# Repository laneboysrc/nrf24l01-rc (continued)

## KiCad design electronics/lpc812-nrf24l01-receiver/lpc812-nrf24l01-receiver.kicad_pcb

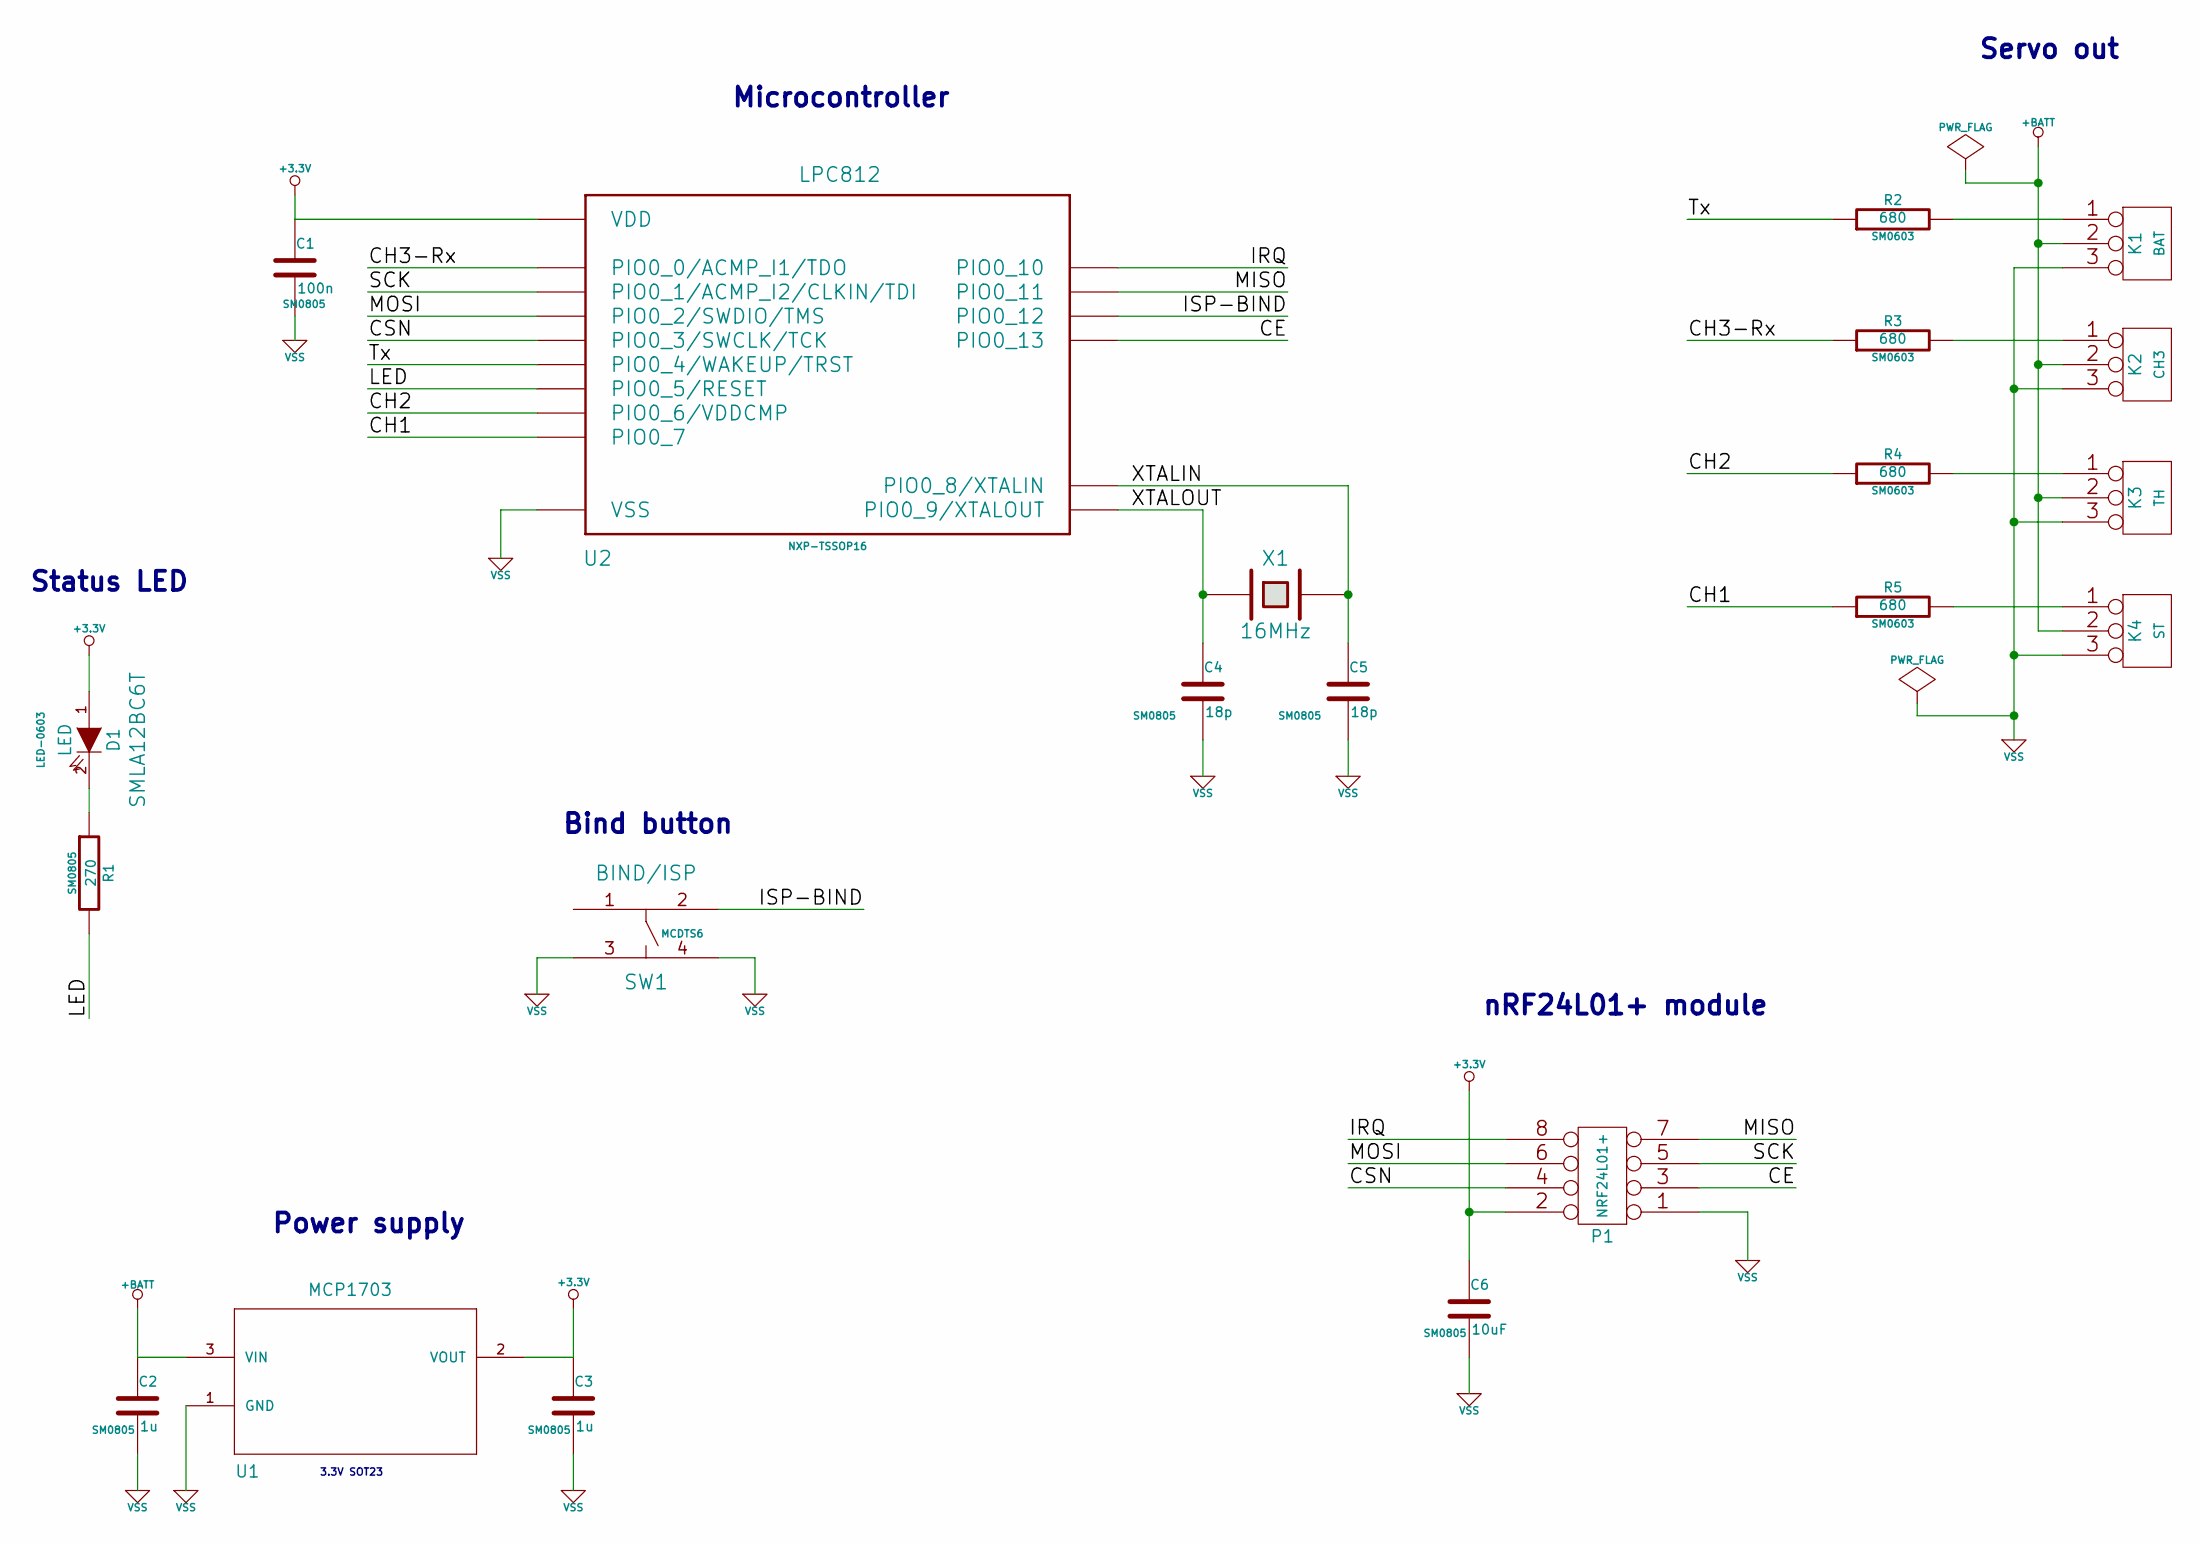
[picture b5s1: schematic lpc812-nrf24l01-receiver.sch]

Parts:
C1: 100n; SM0805
C2, C3: 1u; SM0805
C4, C5: 18p; SM0805
C6: 10uF; SM0805
D1: LED; LED-0603
K1: BAT; PIN_ARRAY_3X1
K2: CH3; PIN_ARRAY_3X1
K3: TH; PIN_ARRAY_3X1
K4: ST; PIN_ARRAY_3X1
P1: NRF24L01+; pin_array_4x2
R1: 270; SM0805
R2, R3, R4, R5: 680; SM0603
SW1: BIND/ISP; MCDTS6
U1: MCP1703; MCP1703-SOT95P300X145-3N
U2: LPC812; NXP-TSSOP16
X1: 16MHz; Q_49U3HMS

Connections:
+3.3V: C1.1, C3.1, C6.1, D1.1 (A), P1.2, U1.2 (VOUT), U2.12 (VDD)
+BATT: C2.1, K1.2 (PM), K2.2 (PM), K3.2 (PM), K4.2 (PM), U1.3 (VIN)
/CE: P1.3, U2.1 (PIO0_13)
/CH1: R5.1, U2.14 (PIO0_7)
/CH2: R4.1, U2.15 (PIO0_6/VDDCMP)
/CH3-Rx: R3.1, U2.16 (PIO0_0/ACMP_I1/TDO)
/CSN: P1.4, U2.5 (PIO0_3/SWCLK/TCK)
/IRQ: P1.8, U2.8 (PIO0_10)
/ISP-BIND: SW1.2, U2.2 (PIO0_12)
/LED: R1.2, U2.3 (PIO0_5/RESET)
/MISO: P1.7, U2.7 (PIO0_11)
/MOSI: P1.6, U2.6 (PIO0_2/SWDIO/TMS)
/SCK: P1.5, U2.9 (PIO0_1/ACMP_I2/CLKIN/TDI)
/Tx: R2.1, U2.4 (PIO0_4/WAKEUP/TRST)
/XTALIN: C5.1, U2.11 (PIO0_8/XTALIN), X1.2
/XTALOUT: C4.1, U2.10 (PIO0_9/XTALOUT), X1.1
unnamed: D1.2 (K), R1.1
unnamed: K4.1, R5.2
unnamed: K3.1, R4.2
unnamed: K2.1, R3.2
unnamed: K1.1, R2.2
VSS: C1.2, C2.2, C3.2, C4.2, C5.2, C6.2, K1.3, K2.3, K3.3, K4.3, P1.1, SW1.3, SW1.4, U1.1 (GND), U2.13 (VSS)

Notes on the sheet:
Microcontroller
Servo out
nRF24L01+ module
Status LED
Bind button
Power supply
3.3V SOT23

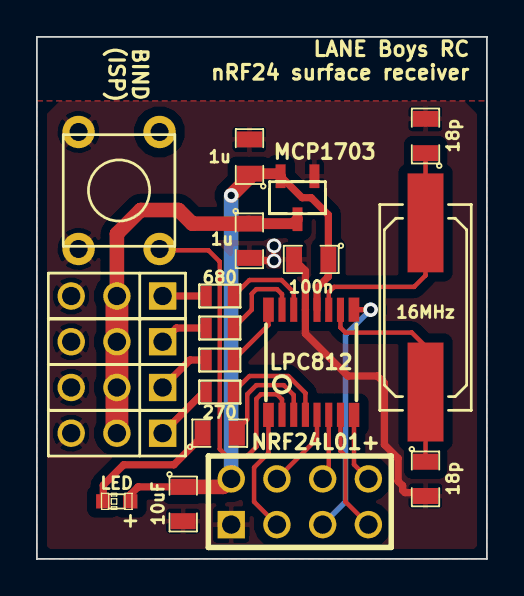
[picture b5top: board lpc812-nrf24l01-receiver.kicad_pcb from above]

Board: 2 copper layers, 25.0 x 29.0 mm, 21 parts (0 on the bottom side), 22 nets.

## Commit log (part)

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2014-11-16 Now can assemble for XR3100 and HKR3000 with IFDEF!
    One source code can generate both firmware versions now.
2014-11-17 Add gitignore file
2014-11-17 Add CPPM match and make system
2014-11-17 Add erasing of the flash pages before flashing
2014-11-18 Add patch to make servo pulses more accurate
    Originally all interrupts were at the same priority. This meant
    that when an interrupt performed some calculation while the
    servo pulse interrupt Timer1 triggered, the servo pulse
    interrupt was delayed and therefore the servo pulse longer
    than desired. This was found to be about 16us -- which is
    quite significant.
2014-11-18 Better directory name
2014-11-18 Start implementing RF and SPI functions
2014-11-18 Add NRF module pin-outs
2014-11-20 Start implementing the rf functions
2014-11-21 Add more comments and cleanup the disassembly
2014-11-21 Introduce platform.h
2014-11-21 Update IO pins
2014-11-21 Make ERC pass
2014-11-21 Add switches library for SMD tact switches we have
2014-11-22 Change pin-out for better layout
2014-11-22 Basic receiver function now working
2014-11-22 Clean up the code and implement calculation of servo pulse
2014-11-23 Add servo outputs
2014-11-23 Output servo pulses only after a valid stick data packet was received after reset
2014-11-23 Add LED output
    Temporarily on another pin
2014-11-23 Tidy up IO port usage via defines
2014-11-23 Implement preprocessor output
2014-11-23 Re-layout the board, add protection resistors
2014-11-24 Make labels local
2014-11-24 Remove switches library, split into separate libraries now.
2014-11-24 Remove duplicate units and tweak schematic symbols
2014-11-24 Start working on the silk screen
2014-11-24 Tweak the footprints and board
2014-11-25 Move NRF programmer ZIP into sub-folder
2014-11-25 Use dummy variable for shell command
2014-11-25 Finalize persistent storage implementation
2014-11-25 Add a startup delay before communicating with the nRF24
2014-11-25 Fix persistent storage reading values back wrongly
2014-11-25 Remove test bind data
2014-11-25 Fix issue with initial delay hanging
2014-11-25 Add item regarding watchdog and brown-out reset
2014-11-25 Re-layout the board with different servo connector positions
2014-11-26 Add idea about running timer at 750ns instead of 1us
2014-11-26 Implement hopping using SCTimer L. Not tested.
2014-11-26 More silk screen tweaking
2014-11-26 Add more info about packets over the air
2014-11-26 Use servo pulse timer clock of 750ns, just like in the nRF24LE1
2014-11-26 Remove watchdog item, not feasible
2014-11-27 Prepare for proper delay for the nRF24L01
2014-11-27 Use Multi Rate Timer to create delays required for operating the nRF24
2014-11-27 Add reconsideration of Watchdog
2014-11-27 Fix via alignmnet, add LED to silk screen
2014-11-27 Tweak silkscreen of LED
2014-11-27 Change components to 0805 which we have in stock
2014-11-27 Test code for hopping and syncing behaviour
2014-11-28 Add define to enable/disable the preprocessor output
2014-11-28 Add CH3 to see receive start flags
2014-11-28 Do not store persistent data in hex file, so we can preserve it while flashing
2014-11-29 Start on NRF24LE1 based receiver hardware
2014-11-29 Work on the layout of the NRF24LE1 receiver
2014-11-29 Checked delay function, remove TODO item
2014-11-29 Use round tact switch, tidy up the board
2014-11-30 Make pinout similar to XR3100
2014-11-30 Add PDF of the schematics
2014-11-30 Continue implementing the NRF24LE1 receiver.
2014-11-30 Implement persistent storage
2014-12-01 Lots of tidying-up and refactoring SPI routines to use less memory
2014-12-01 Add IO initialization and different hardware configurations
2014-12-01 Move our program tools out of the firmware for the programmer
2014-12-01 Fix read register being faulty after refactoring
2014-12-02 Move persistent storage into top of the flash
2014-12-02 Fix page erase process by waiting for WREN to be cleared
2014-12-02 Cleanup. Firmware is working!
2014-12-02 Reverse the PPM output polarity
2014-12-03 More tidying up
2014-12-04 Change brown-out reset level to 2.8V
2014-12-07 Add test of servo pulses
2014-12-12 Major refactoring of directory structure
2014-12-12 Fix spelling
2014-12-13 Add ignore files for build directory
2014-12-13 Add public domain license
2014-12-13 Add build instructions
2014-12-13 Add README for NRF24LE1 source code
2014-12-13 Add README for PCB and schematics
2014-12-14 Update documentation
2014-12-14 Add pre-compiled firmware images
2014-12-14 Add precompiled binaries to repository
2014-12-24 Fix binding procedure legend
2014-12-25 Fix IOs and persistent storage location for actual hardware
2014-12-26 Fix crystal oscillator usage, now working
2014-12-26 Fix preprocessor output, now all working
2014-12-26 Fix preprocessor; not tested yet
2014-12-27 Fix timer documentation and initial servo pulse. repeat time now 10ms
2014-12-27 Update firmware images to latest code changes
2015-01-05 Add 2x 47uF 0805 tantalum bypass cap to combat brown-outs
2016-04-27 Add STM32F1 headless transmitter schematics
2016-04-27 Add architecture document draft
2016-04-27 Add libopencm3 stub
2016-04-28 Move .gitmodules to project root
    Otherwise and error message occurs when doing
    git submodule update --init
    on another computer.
2016-04-28 Improve the makefile
2016-04-28 Add UART1 printf using interrupt and a ring buffer
    Taken from libopencm3 examples
2016-04-28 Optimize periperhal clock enabling
2016-04-28 Add PCB (breadboard simulation) draft.
    Adjust pin-out according to best fit
2016-04-30 Add requirement regarding support of more channels
2016-05-09 Add transmitter overview spreadsheet
2016-05-10 Add mixer design details
2016-05-12 Add placeholders after mixer source code
2016-05-14 Update Futaba and Jomac hardware
2016-05-17 Add architecture diagram
2016-05-18 Remove CFLAGS that may become an issue
2016-05-20 Fix UART, now working
2016-05-22 Add support for GDB debugging
2016-05-22 Use libopencm3 functions to access timers
2016-05-22 PA0 now toggles with the output compare on Timer2 Ch1
2016-05-22 Move TIM2_CH1 to PA15
    Don't forget to disable JTAG!
2016-05-22 Add rudimentary song playback
2016-05-23 Refactor sound for a simpler interface
2016-05-23 Refactor interface for sounds and music yet again
    All songs are now the same as from the Winch controller
2016-05-23 Build skeleton for nRF frames
2016-05-23 Cleanup and add documentation
2016-05-24 Add sublime-text project file
2016-05-24 Fix make list being broken due to introduction of -MD
2016-05-24 Start on implementing the HK310 protocol
2016-05-24 Improve HK310 protocol implementation
2016-05-24 Add curves, ported from Deviation project
2016-05-25 Use SPI2 and make SPI work.
    Not tested with NRF24L01 tet
2016-05-26 Tweak Makefile based on learning from CleanFlight
2016-05-26 Add libopencm3 detection
2016-05-26 Tweak RCC usage
2016-05-27 Send failsafe packets regularly
2016-05-27 Rename build directory to _build
2016-05-27 Move sound related files into subdirectory
2016-05-27 Move mixer related files into mixer/ subdirectory
2016-05-27 Move ring buffer into utils/ subdirectory
2016-05-27 Sort file/path names
2016-05-27 Sort include files by name to keep the source tidy
2016-05-27 Port ADC conversion from Deviation
2016-05-27 Change RF being triggered differently
    Add ADC test function
2016-05-27 Reformat curves code and comments
2016-05-27 Bugfix: sound_timer_frequency needs to be 32 bit wide
2016-05-27 Fix RCC initialization
2016-05-28 Fix data type for ADC input buffer
2016-05-28 Handle NSS ourself and don't turn off the SPI after transfers
2016-05-28 Set power before changing channel. Not that it matters ...
2016-05-28 Run the analog channels through the mixer
    Now the flow corresponds to the architecture.
2016-05-28 Change channel values to -10000..0..10000
2016-05-28 Tidy up the curves code
2016-05-28 Make deadband curve function work
2016-05-28 Add skeleton for limits applied to channels
2016-05-29 Add input logic and stick calibration
2016-05-29 Move all configurable items into config.c
    This is in preparation for the programming box functionality
2016-05-29 Tidy up includes
2016-05-29 Annotate the PCB and increase track widths for better visibility
2016-05-30 Minor tidy-up
2016-05-31 Remove unnecessary EXTI2
2016-05-31 Tweak the music and sounds
2016-05-31 Tidy up SPI code
2016-05-31 Stop binding after a configurable timeout
    This is necessary as the PA in the nRF module from AliExpress
    even boosts the -18dBm signal, leading to a long range where
    the bind data can be received. In order to not interfere with other
    people it is best to keep binding only on for a short time.
2016-05-31 Implement battery alarm
2016-06-04 Add battery life testing Python code
2016-06-04 Add file logging
2016-06-04 Add measurement from an almost empty 800mAh battery until shutoff
2016-06-05 Change battery low leves after testing, move to separate file
2016-06-05 Fix filename for CSV file
2016-06-05 Add documentation and clean-up
2016-06-11 Make new bind address and hop sequence for the DLG
2016-06-11 Update architecture document due to issue with rf power during binding
2016-06-11 Implement channel inversion for output channels
2016-06-11 Move configuration into flash and copy to RAM at startup
    This is in perperation for the programming box
2016-06-11 Fix logging of structure output
2016-06-11 Remove debug printf to verify config_flash address. Working!
2016-06-12 Update TODO list
2016-06-12 Rename background save function
2016-06-12 Add songs made by Patrick for config broken, PB connecting/disconnecting
2016-06-12 Add failsafe config and add music if config is invalid
2016-06-12 Add unused inputs as switches and configure them as inputs
2016-06-13 Remote programming box, was meant for the STM32F1 transmitter
2017-06-26 Add Gerber for revision 2 PCB
2018-08-06 Add 4-channel protocol info
2018-08-07 Implement 4-channel protocol variant
    Not tested yet
2018-09-03 Initialize IP1
    Interrupt priority 1, set Timer1 to highest priority
2018-09-08 Fix servo glitching issue
2018-09-11 Make 8 servo outputs work
2018-09-11 More cleanup and improve documentation
2018-09-12 Clean-up the makefile
2018-09-12 Pull-in rc-receiver code from LPC812 and make it compilable
    No function yet
2018-09-12 Implement 4 channel protocol
    Use TIMER0 for servo output as TIMER2 is used internally in the
    micro ESB code!
2018-09-12 Implement persistent storage
    Not tested yet
2018-09-12 Implement servo setting from receiver function
2018-09-13 Add TX test program for Micro ESB
2018-09-14 Fiddle with receiver, could not get it working with the transmitter
2018-09-14 Work on initial layout
2018-09-18 Add tact switch
2018-09-19 Reposition the components
2018-09-20 Add 3D symbol for the push button
2018-09-21 Optimize trace exit from pins
2018-09-24 More tweaks
2018-09-26 Remove nRF51822 receiver
    Could not get legacy ESB working
2018-09-26 Make better README for differnt LPC812 versions
2018-09-27 Change crystal of 8ch version to 16 MHz
2018-09-28 Add 8 channel GPIOs
    Start refactoring code to switch between 4ch and 8ch version.
2018-09-29 Change crystal to 12 MHz and add schematics annotations
2018-10-08 Tidy up Fab layer
2018-10-14 Add Gerber for Rev 1, manufactured 2018-10-14
2018-10-19 Add bind address
2018-10-25 Chip detection is working and ISP works on long-press bind btn
2018-10-25 Port 4ch support from nRF24LE1 version
    Not tested yet
2018-10-25 Start on 8ch rf protocol details
2018-10-25 Add skeleton for packet decoding
2018-10-25 Fix pinout for both 4ch and 8ch version
    MISO and IRQ are swapped between them
2018-10-26 Implement IO reconfiguration for 4ch and 8ch hardware
2018-10-26 Change LED resistor value
    Update library to latest version of KiCad
2018-11-04 Save id for 8ch protocol
2018-11-04 Remove duplicate code
2018-11-04 Fix output channels in 8ch mode
2018-11-21 Add RF simulation and make receiver work
    Turns out the issue was that CH1 and CH2 had a solder bridge
    on the LPC812...
2018-11-26 Make PLL work for 4CH receiver hardware
